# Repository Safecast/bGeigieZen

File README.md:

# bGeigieZen

A modern radiation monitoring device based on the M5Stack hardware platform, developed by the Safecast community.

## Overview

bGeigieZen is a portable radiation monitoring device that combines precision sensing with a user-friendly interface. Built on the M5Stack platform, it provides real-time radiation measurements with GPS logging capabilities.

## Features

- Real-time radiation monitoring
- GPS location tracking
- Data logging to SD card
- User-friendly display interface
- Long battery life
- Mobile app connectivity
- Compatible with the Safecast API

## Hardware Requirements

- M5Stack Core device (Core2 or CoreS3)
- LND-7317 radiation sensor
- GPS module (see [Supported GPS Modules](#supported-gps-modules) below)
- SD card for logging

## Supported GPS Modules

The firmware supports u-blox GPS modules over UART (Port C on M5Stack).

| Module | Chip | Protocol | Mode | Notes |
|---|---|---|---|---|
| Beitian BN-280 / BN-880 | u-blox M8 | UBX (bidirectional) | Full UBX | Default recommended module |
| u-blox NEO-M9N | u-blox M9 | UBX (bidirectional) | Full UBX | |
| u-blox NEO-M10 | u-blox M10 | UBX (bidirectional) | Full UBX | |
| u-blox NEO-7M / UBX-G7020-KT | u-blox M7 | NMEA (RX-only) or UBX | NMEA fallback or Full UBX | RX-only works with only GPS TX → CoreS3 GPIO18 connected; connect GPS RX → GPIO17 for full UBX |

### Wiring (M5Stack CoreS3 Port C)

| CoreS3 Port C pin | GPIO | Direction | Connect to |
|---|---|---|---|
| RXD | GPIO18 | ESP32 receives | GPS TX |
| TXD | GPIO17 | ESP32 transmits | GPS RX (optional — required for full UBX mode) |

**NMEA fallback mode:** If only the GPS TX → GPIO18 wire is connected (GPS RX is not wired), the firmware automatically detects this and switches to NMEA-only parsing. Coordinates, time, date, and satellite count are still reported. The status bar shows `GPS?` while searching, then the satellite count and fix state once acquired. Full UBX mode (both wires) is recommended for faster cold-start and richer data.

## Software Setup

1. **Install Required Development environment**
   - VS Code with PlatformIO or PlatformIO standalone

2. **Install Required Libraries**:
   - m5stack/M5Unified
   - claypuppet/SensorReporter
   - beakes/TeenyUbloxConnect
   - alextaujenis/RBD_Timer

3. **Clone the Repository**:
   ```bash
   git clone https://github.com/Safecast/bGeigieZen.git
   ```

## Building and Flashing

1. Open the project in VS Code with PlatformIO, or invoke PlatformIO from the shell/CMD.
2. Select your M5Stack board.
3. Compile and upload.

## Usage

1. Power on the device.
2. Wait for GPS signal acquisition.
3. Radiation measurements will display on screen.
4. Data logs automatically save to the SD card.

## Status Bar

The bottom status bar shows live device state at a glance:

| Indicator | Meaning |
|---|---|
| `GPS?` (orange) | GPS active, searching for satellites (cold start) |
| `GPS12` (orange) | GPS tracking 12 satellites, no fix yet |
| `GPS5` (green) | GPS fix acquired using 5 satellites |
| `GPS` (red) | GPS module not detected / error |
| `GM` (white) | Geiger tube active |
| `GM` (red) | Geiger tube required but not detected |
| `SD` (white/green) | SD card present and writeable |
| `SD` (red) | SD card required but missing or unreadable |
| `WF` (white/green) | Wi-Fi connected |
| `BT` (white/green) | Bluetooth active |
| `SN` (green) | Sound enabled |
| `#12345` | Device ID |

## SD card configuration files

This project references configuration files used by both bGeigie Nano and bGeigie Zen devices. They are different and not interchangeable. Use the appropriate file for your device:

### bGeigie Nano — `SAFECAST.TXT`

- Location: SD card root of a bGeigie Nano.
- Format: `key=value` per line. Example reference file: https://github.com/Safecast/bGeigieNanoKit/blob/master/SD%20card/SAFECAST.TXT

Common keys (with firmware semantics):
- `nm` — Profile name. Typically `SAFECAST`. Informational label, shown in menus/log headers.
- `did` — Device ID used by the Safecast ecosystem to associate logs/uploads. Required for proper identification. Range and format depend on Nano firmware and Safecast policy.
- `gt` — GPS type selector. `0` often means u‑blox; other values map to alternative GPS chipsets/modules. Used to configure serial baud, message set, and initialization.
- `gm` — GPS mode. Controls GPS operating/profile mode (e.g., cold/warm start preferences or power mode). Exact mapping is firmware‑specific.
- `cpmf` — CPM calibration factor (numeric). Multiplier applied to raw tube counts to compute calibrated CPM or uSv/h conversion path.
- `cpmn` — CPM factor name (text). Label for the calibration factor (e.g., `Cs137`) stored alongside logs.
- `bqmf` — Bq/m² calibration factor (numeric). Multiplier used when exporting in Bq/m² units.
- `bqmn` — Bq/m² factor name (text). Label for the Bq/m² factor (e.g., `Cs137`).
- `al` — Alert threshold in CPM. When current CPM ≥ `al`, the Nano emits an alert (beep/visual), depending on sound settings.
- `tz` — Timezone offset in hours from UTC. Example: `9` for JST. Used for local time stamping on device.
- `cn` — Country code (ISO‑3166). Often `JPN`, etc. May be embedded in file headers or used for region‑specific defaults.
- `st` — Logging start mode. `0` typically manual; non‑zero values may enable auto‑start or different trigger logic. Firmware‑dependent.
- `ss` — Sound setting. `0` off, `1` on (beeps/clicks). May offer additional levels on some firmware.
- `sh` — Screen brightness (0–100). Backlight level.
- `sm` — Screen/map mode. Selects UI layout or mapping behavior. Firmware‑dependent.
- `cw` — Commit/write interval in seconds. Controls how frequently log lines are flushed to SD.

Notes:
- Values and enumerations above reflect common Nano firmwares; refer to the Nano documentation for the definitive mapping.
- Consult the Nano repository for full semantics and latest defaults.

Sample templates:

- Minimal `SAFECAST.TXT` (Nano):

```ini
nm=SAFECAST
did=5555
al=100
tz=9
ss=1
cw=60
```

- Full `SAFECAST.TXT` example (Nano):

```ini
nm=SAFECAST
did=5555
gt=0
gm=0
cpmf=334
cpmn=Cs137
bqmf=37
bqmn=Cs137
al=100
tz=9
cn=JPN
st=0
ss=1
sh=100
sm=0
cw=60
```

References:
- Canonical example file in Nano kit: https://github.com/Safecast/bGeigieNanoKit/blob/master/SD%20card/SAFECAST.TXT
- Nano project docs and firmware should be consulted for exact enumerations and behavior.

### bGeigie Zen — `SAFEZEN.txt`

Every Zen device uses an SD card with a `SAFEZEN.txt` configuration file placed at the SD root. At minimum, you must set a valid `device_id` for the device to operate.

Quick start:
- See sample files in `SDcard/`:
  - `SDcard/minimal/SAFEZEN.txt` (minimal config with just `device_id`)
  - `SDcard/all_settings/SAFEZEN.txt` (example of all commonly supported fields)
- You can also manage all settings from the device: Menu → Settings (the device can read and write `SAFEZEN.txt`).

Supported settings (key=value per line):
- `version`
  - Optional firmware version marker written by the device. If missing, the current firmware attempts to parse using the latest format.
- `device_id`
  - Required. Must be between 5000 and 5999. The device will not operate without a valid ID in this range.
- `user_name`
  - Optional display and identification name used on-screen and in some outputs.
- `api_key`
  - Optional Safecast API key for uploading where applicable. The same key is used for api.safecast.org and simplemap.safecast.org.
- `simplemap_email`
  - Optional. Email address of your simplemap.safecast.org account. Together with `api_key` it is used to log in to simplemap and upload Real-time trip logs there (see `userdocs/rt-trip-logging.md`). If empty, trips are still uploaded to api.safecast.org but the simplemap step is retried and fails. Must come after `device_id` in the file, no spaces.
- `access_point_password`
  - Password for the device’s built-in Wi‑Fi Access Point (used by the configuration portal).
- `wifi_ssid`
  - Primary Wi‑Fi SSID for connecting to a local network.
- `wifi_password`
  - Password for `wifi_ssid`.
- `wifi_ssid2`
  - Secondary Wi‑Fi SSID profile (optional).
- `wifi_password2`
  - Password for `wifi_ssid2`.
- `wifi_profile`
  - Select active Wi‑Fi profile. `1` = use `wifi_ssid`/`wifi_password`. `2` = use `wifi_ssid2`/`wifi_password2`.
- `alert_threshold`
  - CPM alert threshold. Range 10–9999. Triggers audible and visual “CPM ALERT” when exceeded.
  - Note: Older examples may show `alarm_threshold`, but the current firmware uses `alert_threshold`.
  - See: [Zen Specification — Alerts](https://github.com/Safecast/bGeigieZen/wiki/Specification)
- `display_cpm`
  - Display unit selector. `1` = show CPM. `0` = show µSv/h.
- `manual_logging`
  - Logging behavior. `1` = manual start/stop. `0` = automatic depending on mode/movement.
  - See: [Zen Specification — Logging](https://github.com/Safecast/bGeigieZen/wiki/Specification)
- `enable_journal`
  - Enable the journal log. `1` = enabled, `0` = disabled.
  - See: [Zen Specification — Files & Journaling](https://github.com/Safecast/bGeigieZen/wiki/Specification)
- `log_void`
  - Include invalid/void lines in logs. `1` = include, `0` = exclude.
- `screen_dim_timeout`
  - Seconds of inactivity before screen dims.
  - See: [Zen Specification — Display & Power](https://github.com/Safecast/bGeigieZen/wiki/Specification)
- `screen_off_timeout`
  - Seconds of inactivity before screen turns off.
  - See: [Zen Specification — Display & Power](https://github.com/Safecast/bGeigieZen/wiki/Specification)
- `animated_screensaver`
  - Screensaver animation on dim/off. `1` = enabled, `0` = disabled.
  - See: [Zen Specification — Display & Power](https://github.com/Safecast/bGeigieZen/wiki/Specification)
- `error_alert_sound`
  - Error beep sounds. `1` = enabled, `0` = disabled.
  - See: [Zen Specification — Alerts](https://github.com/Safecast/bGeigieZen/wiki/Specification)
- `dim_brightness`
  - Brightness level (0–100) used while dimmed/screensaver.
- `audio_volume`
  - Global audio volume (0–100) for clicks and alerts.
- `fixed_latitude`
  - Latitude used in Fixed mode.
- `fixed_longitude`
  - Longitude used in Fixed mode.
- `fixed_range`
  - Radius in km for Fixed mode validity.
- `dop_max`
  - Maximum acceptable Dilution of Precision (DOP) for GPS fix validity.
  - See: [Zen Specification — GPS & Accuracy](https://github.com/Safecast/bGeigieZen/wiki/Specification)

Notes:
- Unknown or unsupported lines are ignored by the firmware.
- Settings changed from the device UI are persisted to internal memory and can be written back to `SAFEZEN.txt` via Settings → “Save to SD”.
- The device also supports configuring via Wi‑Fi using the built-in Access Point or a local network (see Settings screen).

### Nano ↔ Zen quick comparison (overlapping concepts)

| Concept | bGeigie Nano (SAFECAST.TXT) | bGeigie Zen (SAFEZEN.txt) |
| --- | --- | --- |
| Device ID | `did` (format/range Nano‑specific) | `device_id` (required, 5000–5999) |
| Alert threshold (CPM) | `al` | `alert_threshold` |
| Timezone | `tz` (hours offset) | not required; Zen uses RTC and can show local time; timezone not needed for logging |
| Display units | n/a (Nano UI dependent) | `display_cpm` (1=CPM, 0=µSv/h) |
| Wi‑Fi/API | n/a in Nano SAFECAST | `wifi_*`, `api_key`, `access_point_password` |
| Logging behavior | `st`/`cw` (start mode and commit interval) | `manual_logging` (manual vs auto), commit policy handled by firmware |
| GPS accuracy threshold | n/a (implicit) | `dop_max` (DOP limit) |
| Fixed location | n/a | `fixed_latitude`, `fixed_longitude`, `fixed_range` |
| Brightness & power | `sh` (0–100) | `dim_brightness`, `screen_dim_timeout`, `screen_off_timeout`, `animated_screensaver` |
| Sound & alerts | `ss` (0/1) | `error_alert_sound`, `audio_volume`, `alert_threshold` |

Tip: These files are not interchangeable. Use `SAFECAST.TXT` on Nano, and `SAFEZEN.txt` on Zen.

## Contributing

We welcome contributions! Please follow these steps:

1. Fork the repository.
2. Create a feature branch.
3. Submit a Pull Request.

## License

This project is licensed under the MIT License.

## Support

- Visit [Safecast.org](https://safecast.org)
- Join our community forums
- Report issues on GitHub

## Credits

Developed and maintained by the Safecast community.

- Specifications: [bGeigieZen Wiki](https://github.com/Safecast/bGeigieZen/wiki/Specification)
- Full documentation: [bgeigiezen.safecast.jp](https://bgeigiezen.safecast.jp)

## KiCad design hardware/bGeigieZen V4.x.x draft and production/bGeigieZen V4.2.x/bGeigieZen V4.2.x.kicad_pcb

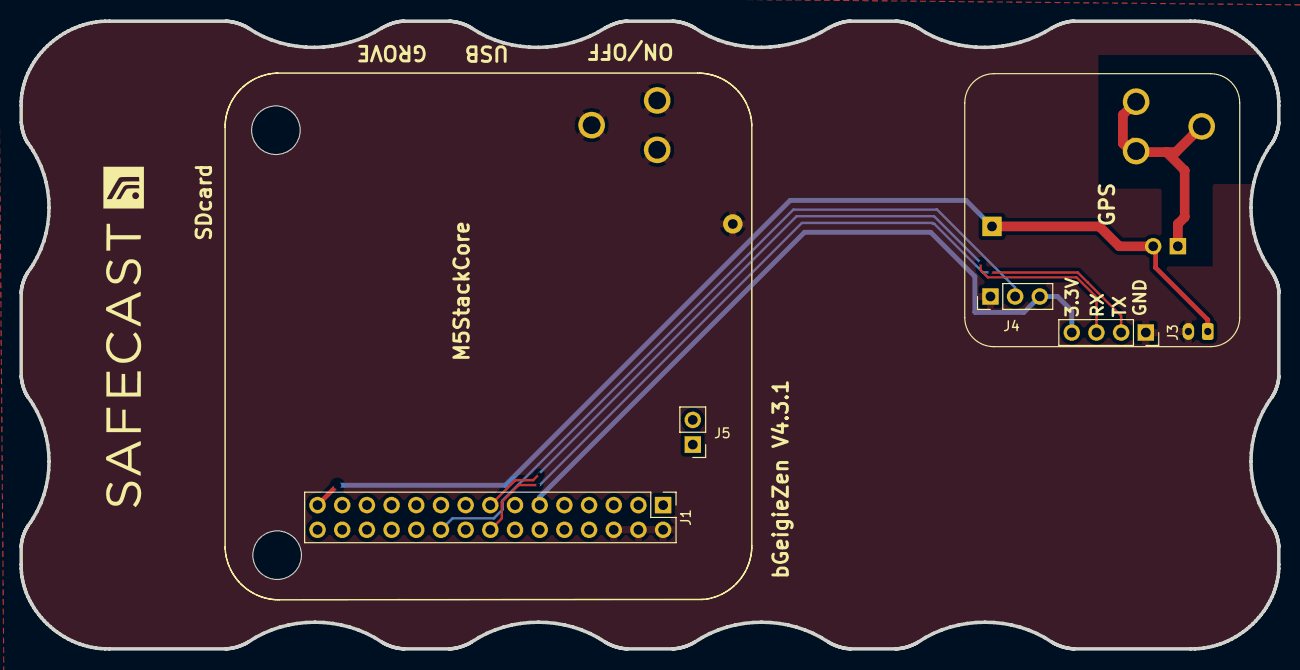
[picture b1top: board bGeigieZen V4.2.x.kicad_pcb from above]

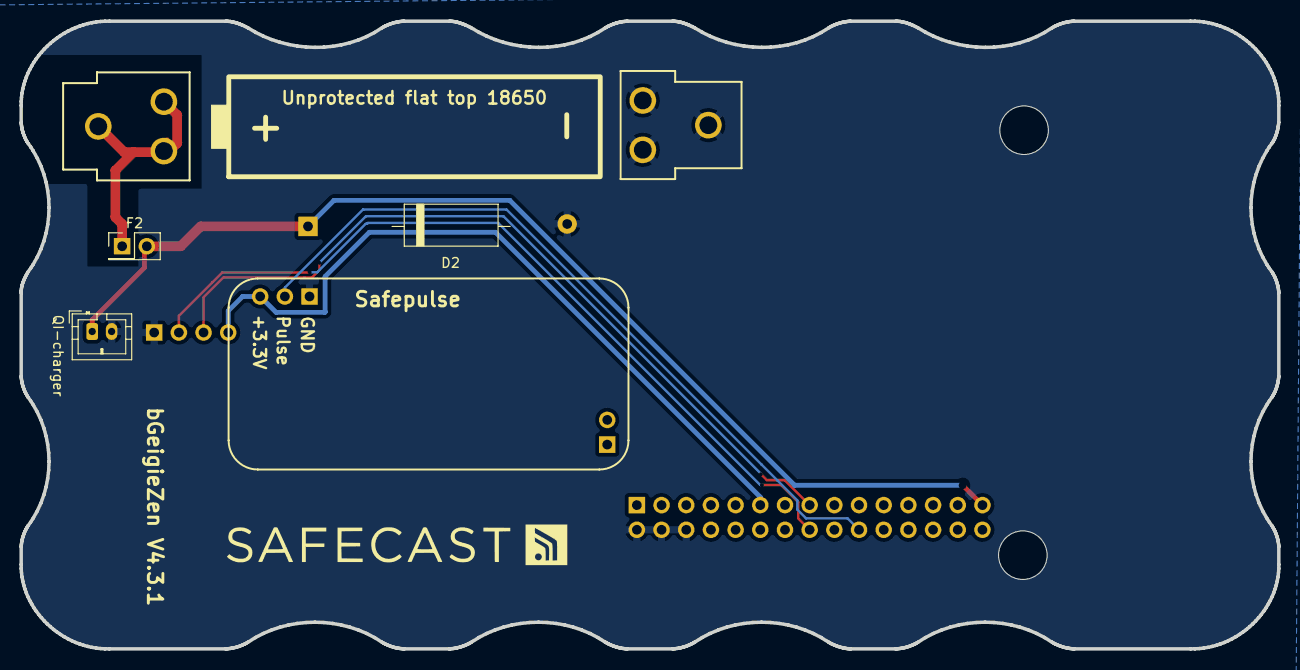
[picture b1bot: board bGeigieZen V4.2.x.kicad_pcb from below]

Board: 2 copper layers, 129.4 x 64.6 mm, 12 parts (5 on the bottom side), 7 nets.

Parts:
BT1: 3.7 V Lipo; BATTERY_18650-HOLDER
D2: Crowbar; D_DO-201_P15.24mm_Horizontal
F2: Polyfuse; PinHeader_2x01_P2.54mm_Vertical
G back: LOGO
G front: LOGO
H4, H6: MountingHole_Pad; MountingHole_3.2mm_M3
J1: M5 2x15 pin; PinHeader_2x15_P2.54mm_Vertical
J3: GPS; PinSocket_1x04_P2.54mm_Vertical
J4: Geiger Safepulse; PinHeader_1x03_P2.54mm_Vertical
J5: Extra support header; PinHeader_1x02_P2.54mm_Vertical
QI-charger: QI GND; JST_PH_B2B-PH-K_1x02_P2.00mm_Vertical

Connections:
3.3V: J1.11, J3.4, J4.3
/BAT: D2.1 (K), F2.2, J1.29, QI-charger.1
/GIO2 on Core and GIO32 on Core-2: J1.20, J4.2
/RX2: J1.15, J3.3
/TX2: J1.16, J3.2
GND: BT1.1 (+), BT1.PWR@2, BT1.PWR@3, D2.2 (A), J1.2, J1.4, J1.6, J3.1, J4.1, QI-charger.2
unnamed: BT1.1 (+), F2.1

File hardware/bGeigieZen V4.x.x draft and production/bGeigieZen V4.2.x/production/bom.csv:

Designator,Footprint,Quantity,Value,LCSC Part #
BT1,BATTERY_18650-HOLDER,1,3.7 V Lipo,
D2,D_DO-201_P15.24mm_Horizontal,1,Crowbar,
F2,PinHeader_2x01_P2.54mm_Vertical,1,Polyfuse,
"H4, H6",MountingHole_3.2mm_M3,2,MountingHole_Pad,
J1,PinHeader_2x15_P2.54mm_Vertical,1,M5 2x15 pin,
J3,PinSocket_1x04_P2.54mm_Vertical,1,GPS,
J4,PinHeader_1x03_P2.54mm_Vertical,1,Geiger Safepulse,
J5,PinHeader_1x02_P2.54mm_Vertical,1,Extra support header,
QI-CHARGER,JST_PH_B2B-PH-K_1x02_P2.00mm_Vertical,1,QI GND,

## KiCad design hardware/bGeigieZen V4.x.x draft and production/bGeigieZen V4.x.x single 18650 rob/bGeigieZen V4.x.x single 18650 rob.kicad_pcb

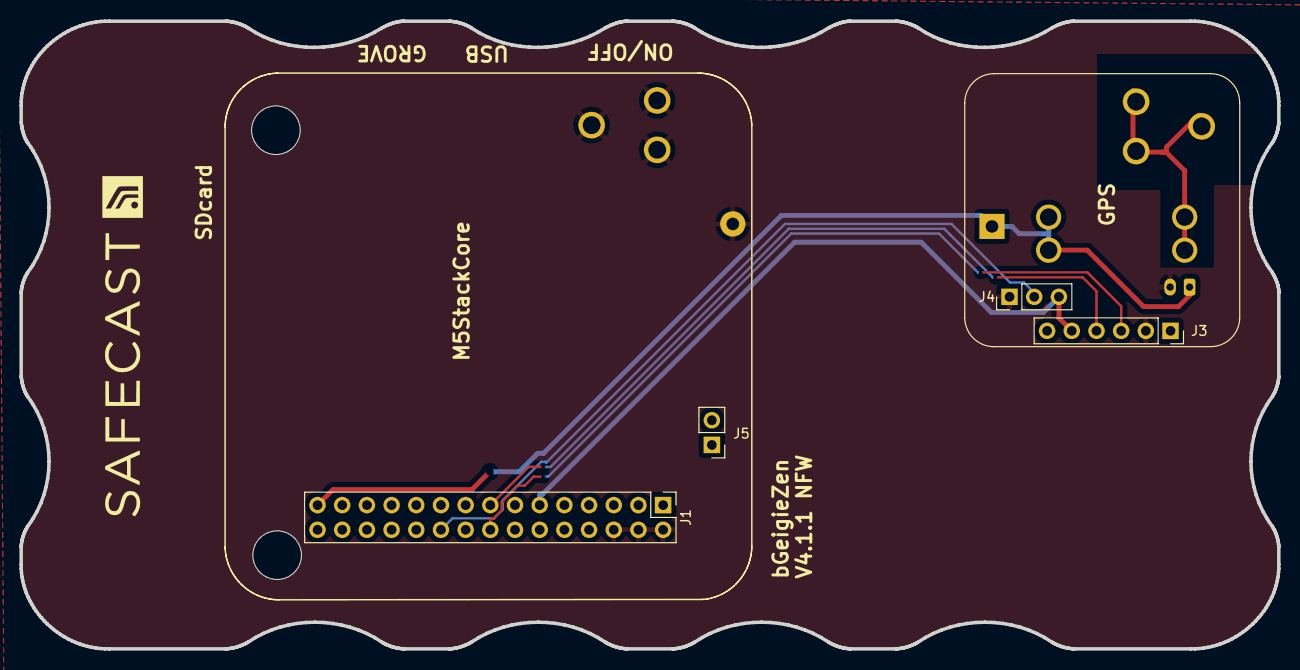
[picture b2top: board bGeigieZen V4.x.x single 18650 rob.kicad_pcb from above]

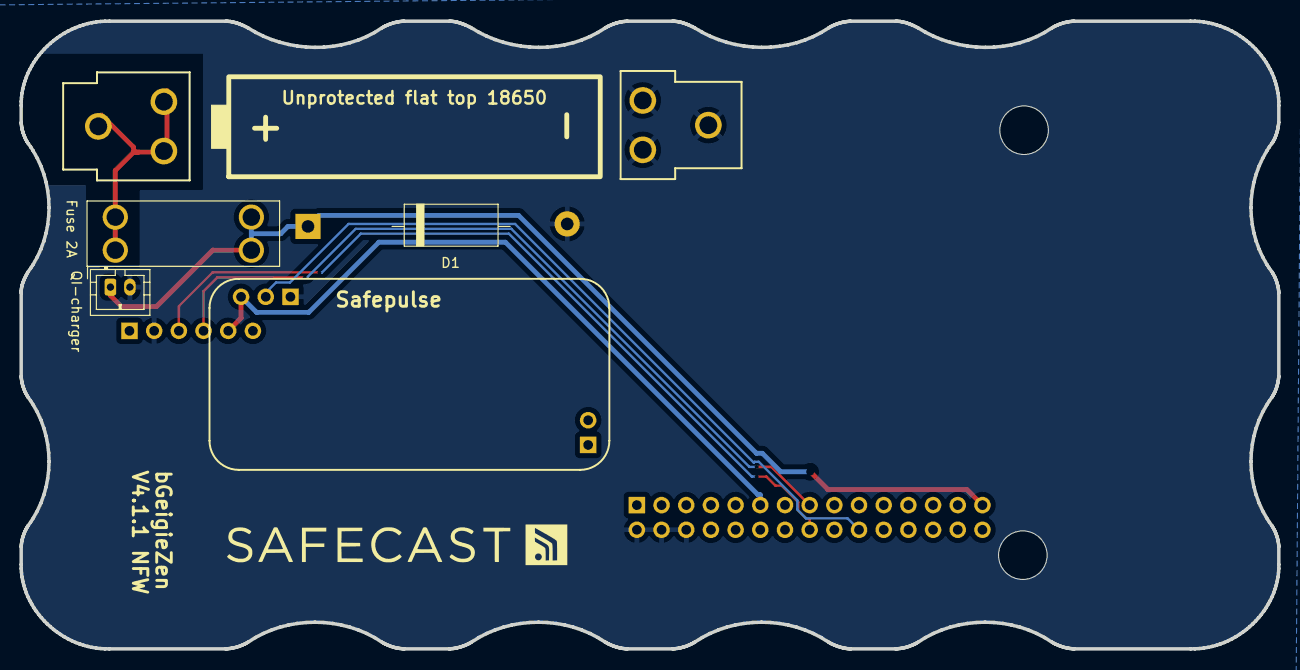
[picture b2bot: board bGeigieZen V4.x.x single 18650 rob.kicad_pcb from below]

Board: 2 copper layers, 129.4 x 64.6 mm, 12 parts (5 on the bottom side), 7 nets.

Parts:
BT1: 3.7 V Lipo; BATTERY_18650-HOLDER
D1: Crowbar; D_DO-201_P15.24mm_Horizontal
Fuse 2A: Fuse_Small; FUSE_3557-2
G back: LOGO
G front: LOGO
H4, H6: MountingHole_Pad; MountingHole_3.2mm_M3
J1: M5 2x15 pin; PinHeader_2x15_P2.54mm_Vertical
J3: GPS; PinSocket_1x06_P2.54mm_Vertical
J4: Geiger Safepulse; PinHeader_1x03_P2.54mm_Vertical
J5: Extra support header; PinHeader_1x02_P2.54mm_Vertical
QI-charger: QI GND; JST_PH_B2B-PH-K_1x02_P2.00mm_Vertical

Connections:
3.3V: J1.11, J3.5, J4.3
/BAT: D1.1 (K), Fuse 2A.2, J1.29, QI-charger.1
/GIO2 on Core and GIO32 on Core-2: J1.20, J4.2
/RX2: J1.15, J3.4
/TX2: J1.16, J3.3
GND: BT1.1 (+), BT1.PWR@2, BT1.PWR@3, D1.2 (A), J1.2, J1.4, J1.6, J3.2, J4.1, QI-charger.2
unnamed: BT1.1 (+), BT1.PWR@2, BT1.PWR@3, Fuse 2A.1

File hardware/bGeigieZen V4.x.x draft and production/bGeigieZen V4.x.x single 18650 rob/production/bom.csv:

Designator,Footprint,Quantity,Value,LCSC Part #
BT1,BATTERY_18650-HOLDER,1,3.7 V Lipo,
D1,D_DO-201_P15.24mm_Horizontal,1,Crowbar,
FUSE 2A,FUSE_3557-2,1,Fuse_Small,
"H4, H6",MountingHole_3.2mm_M3,2,MountingHole_Pad,
J1,PinHeader_2x15_P2.54mm_Vertical,1,M5 2x15 pin,
J3,PinSocket_1x06_P2.54mm_Vertical,1,GPS,
J4,PinHeader_1x03_P2.54mm_Vertical,1,Geiger Safepulse,
J5,PinHeader_1x02_P2.54mm_Vertical,1,Extra support header,
QI-CHARGER,JST_PH_B2B-PH-K_1x02_P2.00mm_Vertical,1,QI GND,

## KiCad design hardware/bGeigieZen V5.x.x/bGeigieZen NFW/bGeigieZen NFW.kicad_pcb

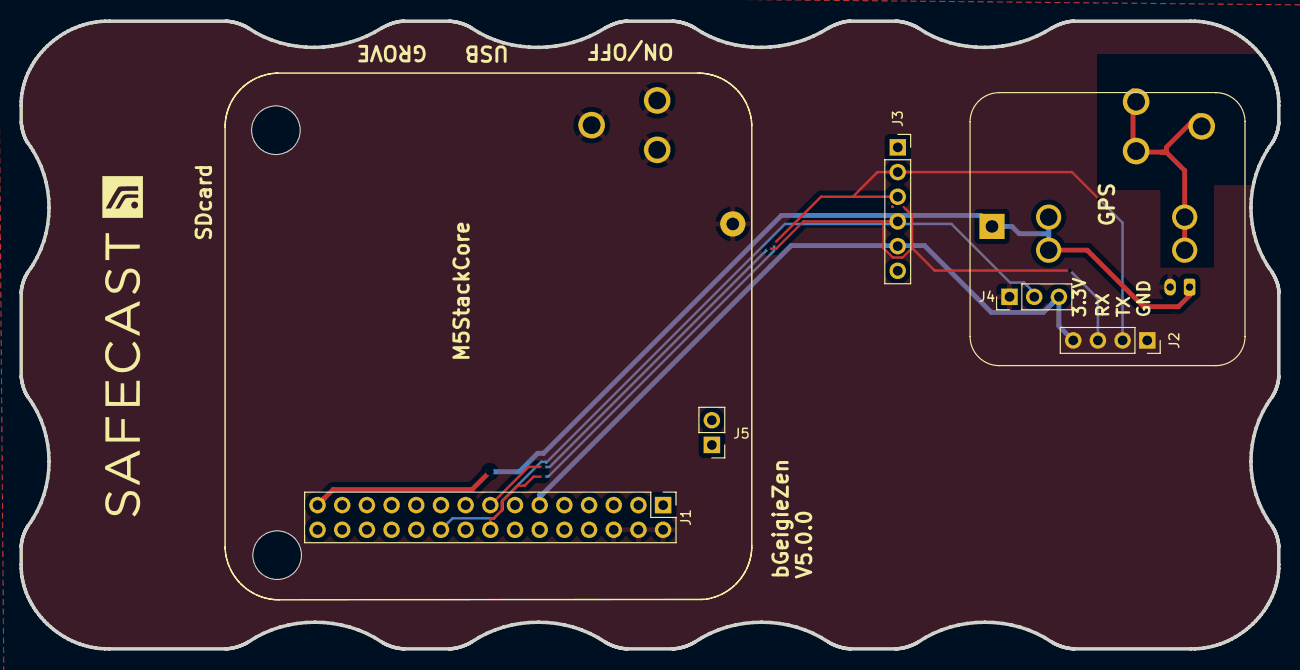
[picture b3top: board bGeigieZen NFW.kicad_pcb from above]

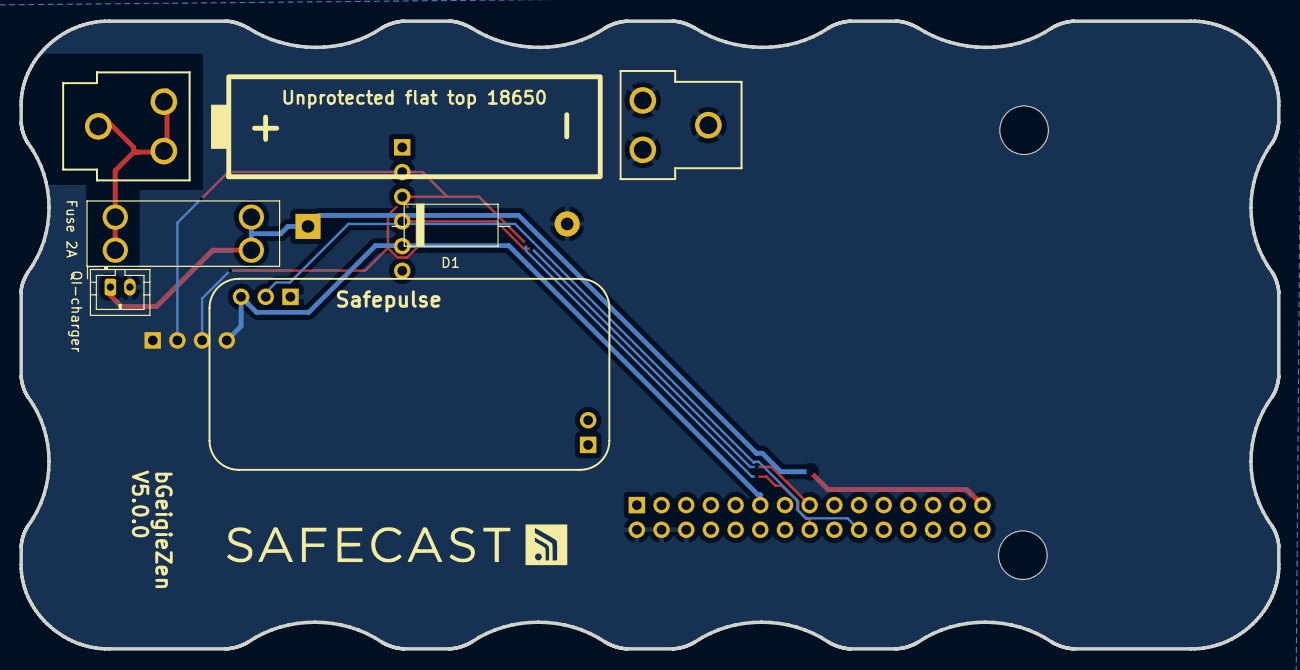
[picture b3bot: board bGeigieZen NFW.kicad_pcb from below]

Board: 2 copper layers, 129.4 x 64.6 mm, 13 parts (5 on the bottom side), 7 nets.

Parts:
BT1: 3.7 V Lipo; BATTERY_18650-HOLDER
D1: Crowbar; D_DO-201_P15.24mm_Horizontal
Fuse 2A: Fuse_Small; FUSE_3557-2
G back: LOGO
G front: LOGO
H4, H6: MountingHole_Pad; MountingHole_3.2mm_M3
J1: M5 2x15 pin; PinHeader_2x15_P2.54mm_Vertical
J2: GPS; PinSocket_1x04_P2.54mm_Vertical
J3: Notecard; PinSocket_1x06_P2.54mm_Vertical
J4: Geiger Safepulse; PinHeader_1x03_P2.54mm_Vertical
J5: Extra support header; PinHeader_1x02_P2.54mm_Vertical
QI-charger: QI GND; JST_PH_B2B-PH-K_1x02_P2.00mm_Vertical

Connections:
3.3V: J1.11, J2.4, J3.4, J4.3
/BAT: D1.1 (K), Fuse 2A.2, J1.29, QI-charger.1
/GIO2 on Core and GIO32 on Core-2: J1.20, J4.2
/RX2: J1.15, J2.3, J3.3
/TX2: J1.16, J2.2, J3.2
GND: D1.2 (A), J1.2, J1.4, J1.6, J2.1, J3.1, J4.1, QI-charger.2
unnamed: BT1.1 (+), Fuse 2A.1

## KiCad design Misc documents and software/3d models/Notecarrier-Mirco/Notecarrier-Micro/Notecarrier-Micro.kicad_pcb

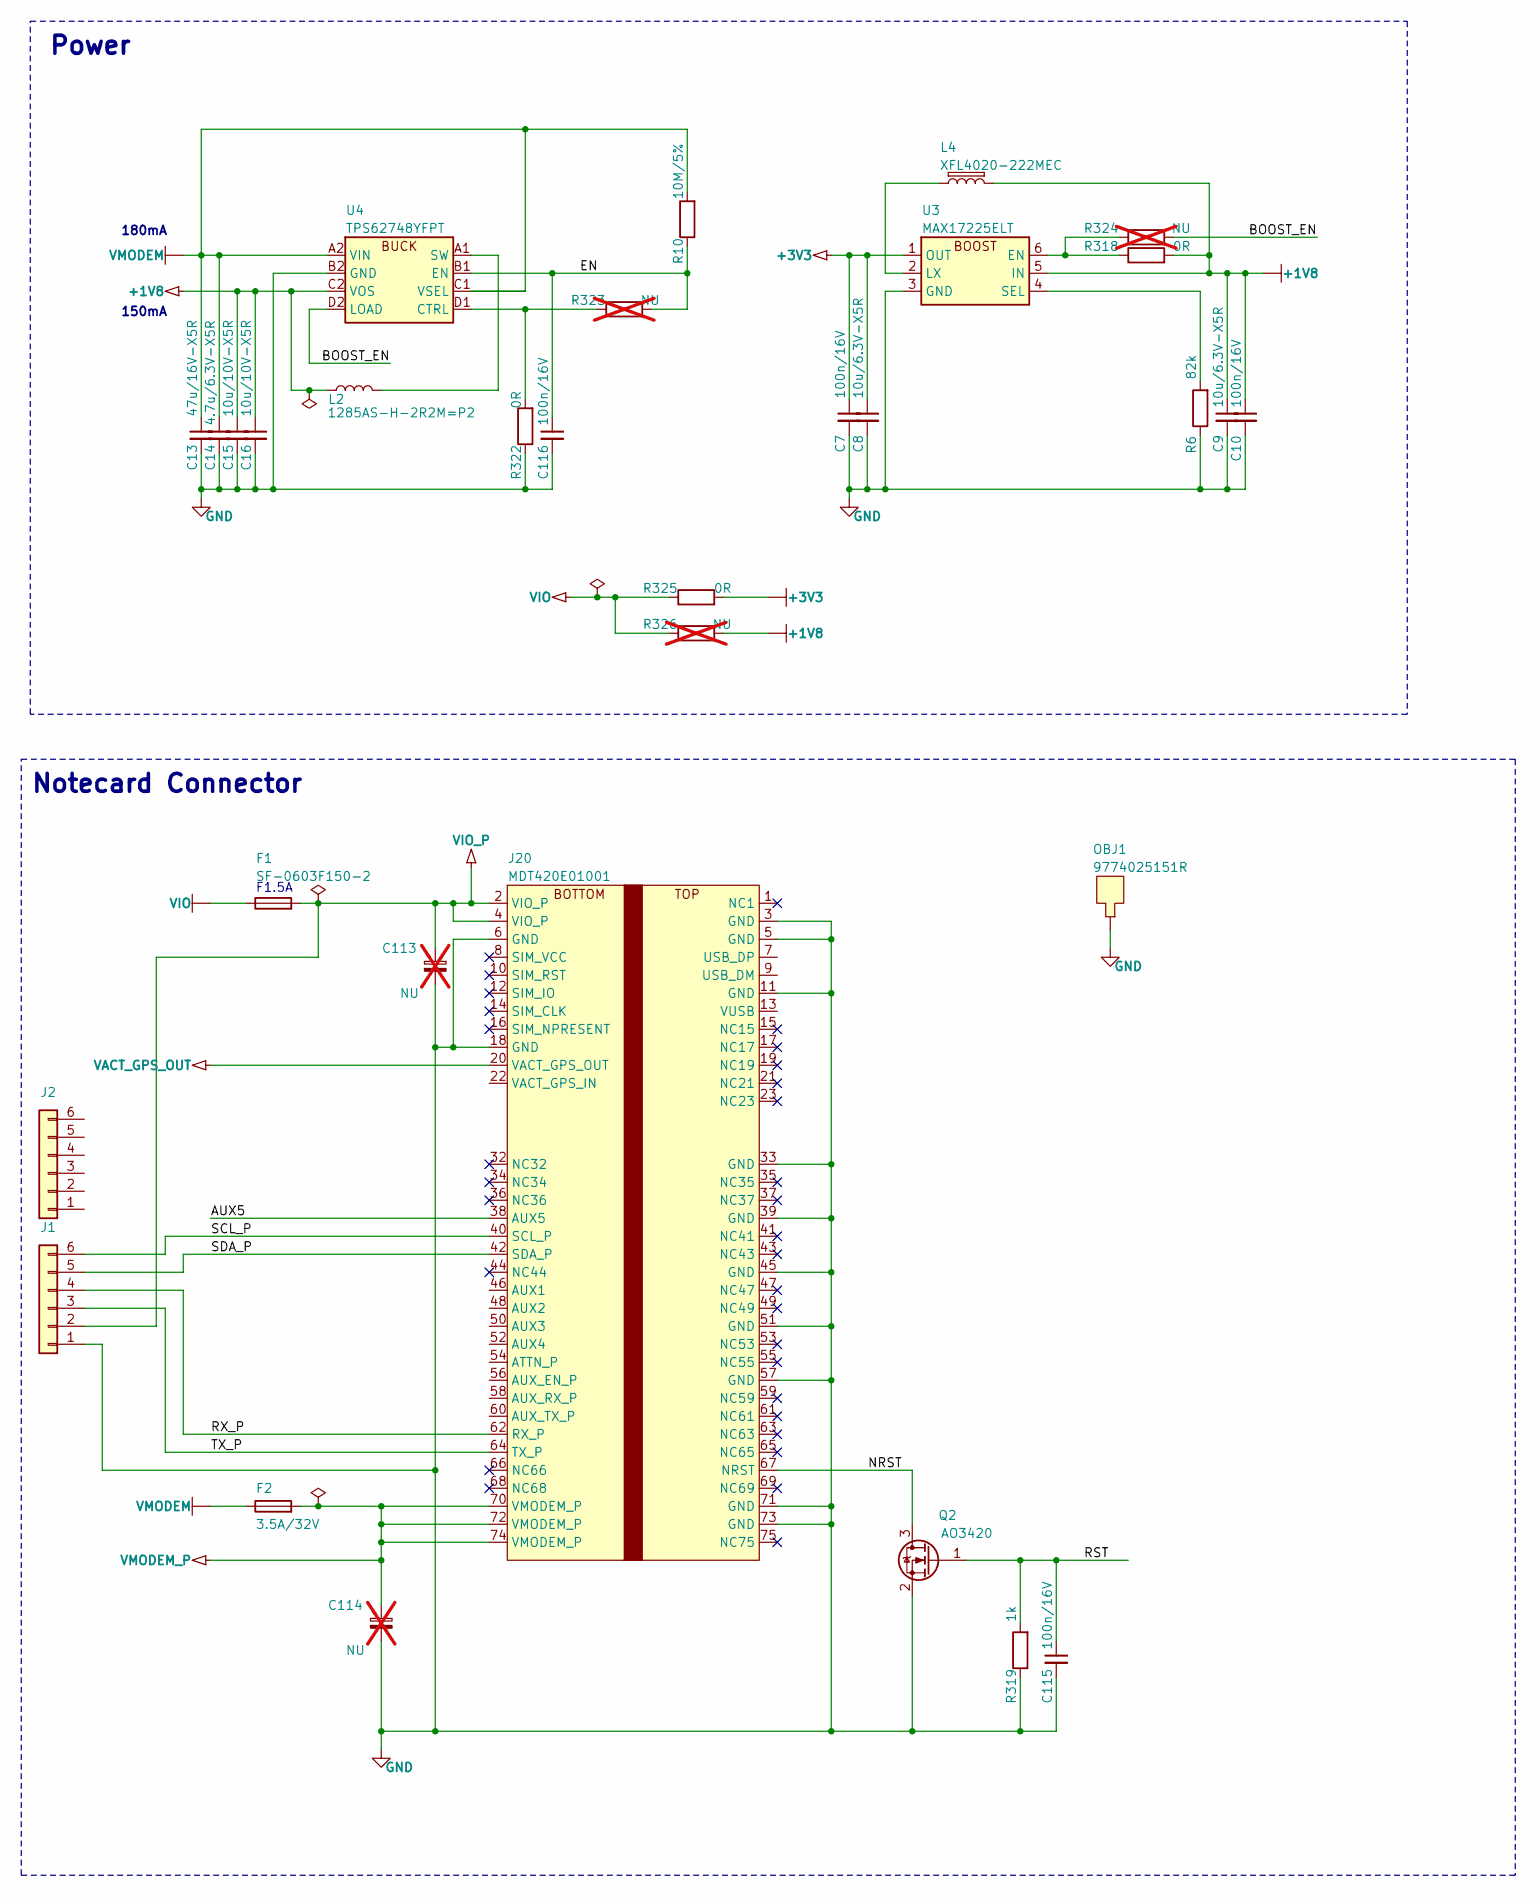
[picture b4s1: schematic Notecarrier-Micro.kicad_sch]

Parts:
C7, C10, C115, C116: 100n/16V; CS-C-0402_NO-FILL
C8, C9: 10u/6.3V-X5R; CS-C-0402_NO-FILL
C13: 47u/16V-X5R; CS-C-1206
C14: 4.7u/6.3V-X5R; CS-C-0402_NO-FILL
C15, C16: 10u/10V-X5R; CS-C-0603
C113: NU; CS-T-A; MPN F930J107KAA; not fitted
C114: NU; CS-T-B; MPN F930J227KBA; not fitted
F1: SF-0603F150-2; FS-0603; MPN SF-0603F150-2
F2: 3.5A/32V; FS-0603; MPN 0603SFV350F/32-2
J1, J2: Conn_01x06; PinHeader_1x06_P2.54mm_Vertical
J20: MDT420E01001; J-75-0050-MOS-M2-E
L2: 1285AS-H-2R2M=P2; LS-0806; MPN 1285AS-H-2R2M=P2
L4: XFL4020-222MEC; LS-XFL4020; MPN XFL4020-222MEC
OBJ1: 9774025151R; DIST-WASMSIM0250
Q2: AO3420; SOT23_NO-FILL
R6: 82k; RS-0402_NO-FILL
R10: 10M/5%; RS-0402_NO-FILL
R318, R322, R325: 0R; RS-0402_NO-FILL
R319: 1k; RS-0402_NO-FILL
R323, R324, R326: NU; RS-0402_NO-FILL; not fitted
U3: MAX17225ELT; WDFN6-0200X0200; MPN MAX17225ELT+T
U4: TPS62748YFPT; XFBGA8; MPN TPS62748YFPT

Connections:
+1V8: C9.1, C10.1, C15.1, C16.1, L2.2, L4.2, R318.2, R326.2, U3.5 (IN), U4.C2 (VOS)
+3V3: C7.1, C8.1, R325.2, U3.1 (OUT)
/AUX5: J20.38 (AUX5)
/BOOST_EN: R324.2, U4.D2 (LOAD)
/EN: C116.1, R10.1, R323.2, U4.B1 (EN)
/NRST: J20.67 (NRST), Q2.3 (D)
/RST: C115.1, Q2.1 (G), R319.2
/RX_P: J1.4, J20.62 (RX_P)
/SCL_P: J1.6, J20.40 (SCL_P)
/SDA_P: J1.5, J20.42 (SDA_P)
/TX_P: J1.3, J20.64 (TX_P)
GND: C7.2, C8.2, C9.2, C10.2, C13.2, C14.2, C15.2, C16.2, C113.2, C114.2, C115.2, C116.2, J1.1, J20.3 (GND), J20.5 (GND), J20.6 (GND), J20.11 (GND), J20.18 (GND), J20.33 (GND), J20.39 (GND), J20.45 (GND), J20.51 (GND), J20.57 (GND), J20.71 (GND), J20.73 (GND), OBJ1.1, Q2.2 (S), R6.1, R319.1, R322.1, U3.3 (GND), U4.B2 (GND)
unnamed: R318.1, R324.1, U3.6 (EN)
unnamed: L4.1, U3.2 (LX)
unnamed: R6.2, U3.4 (SEL)
unnamed: R322.2, R323.1, U4.D1 (CTRL)
unnamed: L2.1, U4.A1 (SW)
VACT_GPS_OUT: J20.20 (VACT_GPS_OUT)
VIO: F1.1, R325.1, R326.1
VIO_P: C113.1, F1.2, J1.2, J20.2 (VIO_P), J20.4 (VIO_P)
VMODEM: C13.1, C14.1, F2.1, R10.2, U4.A2 (VIN), U4.C1 (VSEL)
VMODEM_P: C114.1, F2.2, J20.70 (VMODEM_P), J20.72 (VMODEM_P), J20.74 (VMODEM_P)

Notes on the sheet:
150mA
180mA
F1.5A
Notecard Connector
Power

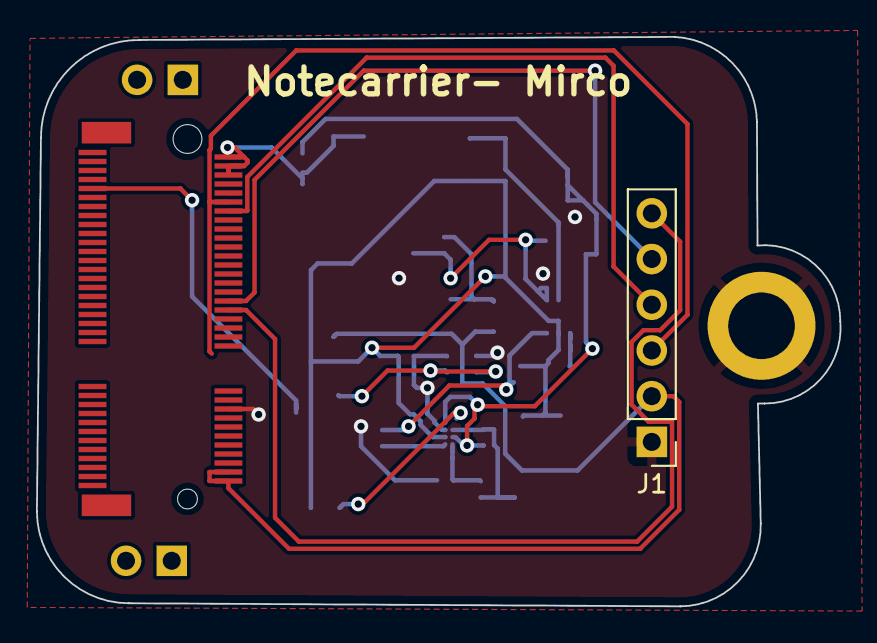
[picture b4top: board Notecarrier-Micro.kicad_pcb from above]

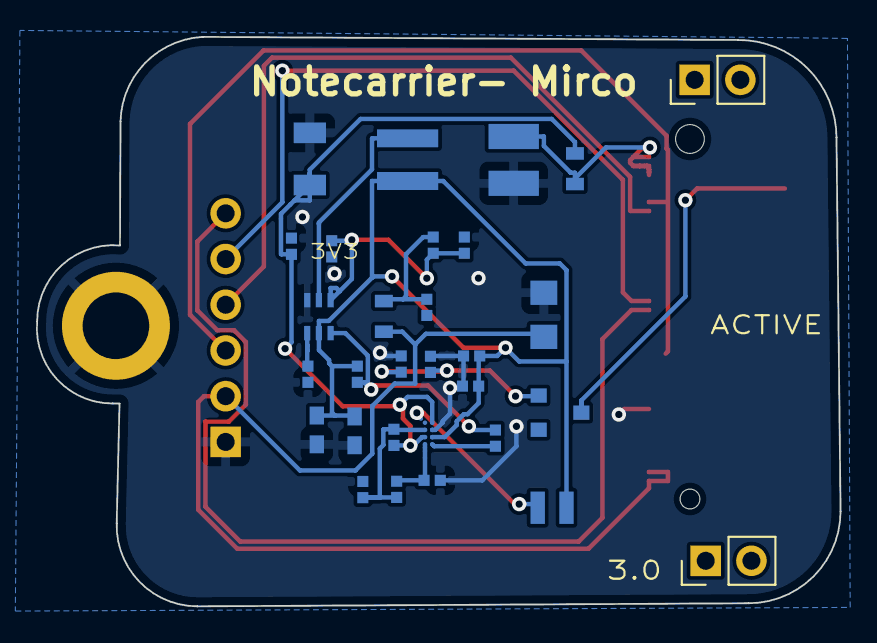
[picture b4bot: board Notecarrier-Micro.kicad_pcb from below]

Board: 11 copper layers, 44.6 x 31.6 mm, 33 parts (30 on the bottom side), 20 nets.

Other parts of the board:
Extra_pin_1, Extra_pin_2: PinHeader_1x02_P2.54mm_Vertical

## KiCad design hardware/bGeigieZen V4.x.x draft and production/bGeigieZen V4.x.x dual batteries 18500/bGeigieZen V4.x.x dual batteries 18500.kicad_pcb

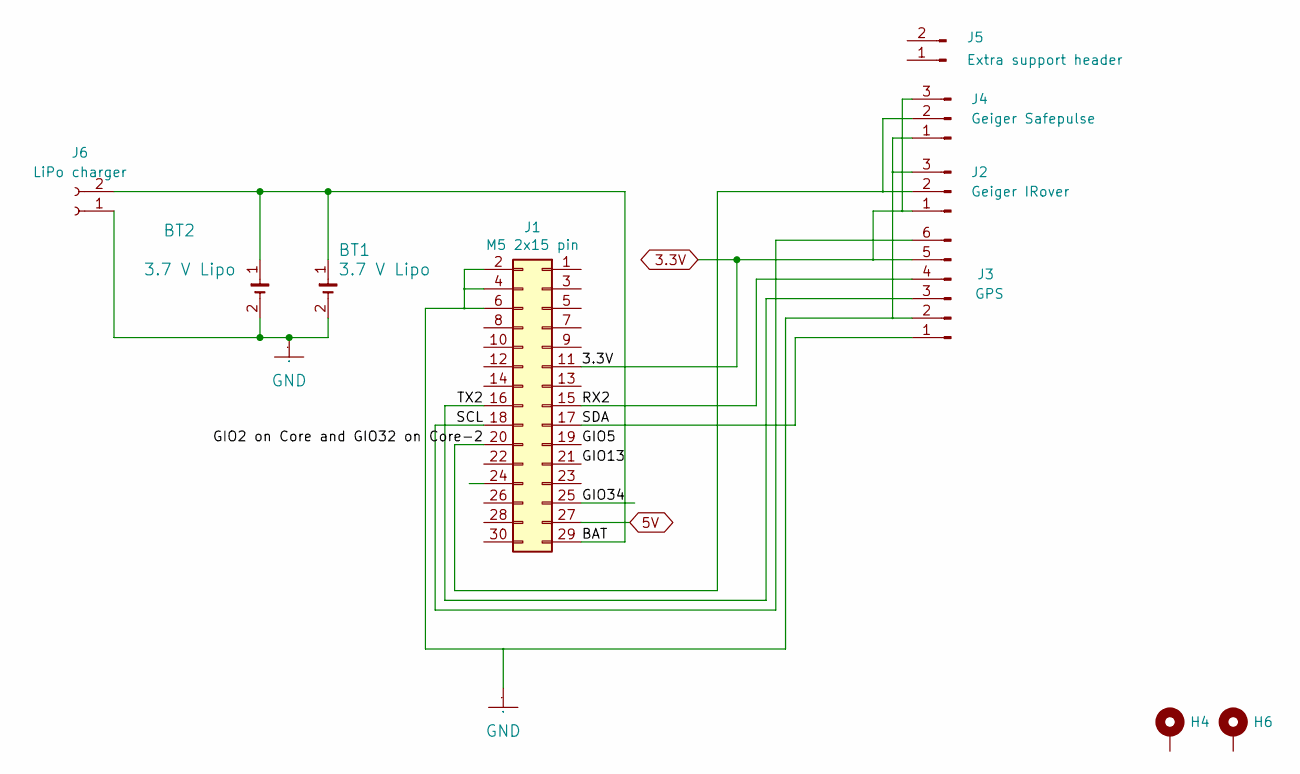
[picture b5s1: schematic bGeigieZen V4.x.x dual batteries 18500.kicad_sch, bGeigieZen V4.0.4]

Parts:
BT1, BT2: 3.7 V Lipo; BATTERY_18650-HOLDER
H4, H6: MountingHole_Pad; MountingHole_3.2mm_M3
J1: M5 2x15 pin; PinHeader_2x15_P2.54mm_Vertical
J2: Geiger IRover; PinHeader_1x03_P2.54mm_Vertical
J3: GPS; PinSocket_1x06_P2.54mm_Vertical
J4: Geiger Safepulse; PinHeader_1x03_P2.54mm_Vertical
J5: Extra support header; PinHeader_1x02_P2.54mm_Vertical
J6: LiPo charger; JST_PH_B2B-PH-K_1x02_P2.00mm_Vertical

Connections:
3.3V: J1.11, J2.1, J3.5, J4.3
5V: J1.27
/BAT: BT1.1 (+), BT2.1 (+), J1.29, J6.2
/GIO2 on Core and GIO32 on Core-2: J1.20, J2.2, J4.2
/GIO5: J1.19
/GIO13: J1.21
/GIO34: J1.25
/RX2: J1.15, J3.4
/SCL: J1.18, J3.6
/SDA: J1.17, J3.1
/TX2: J1.16, J3.3
GND: BT1.2 (-), BT2.2 (-), J1.2, J1.4, J1.6, J2.3, J3.2, J4.1, J6.1

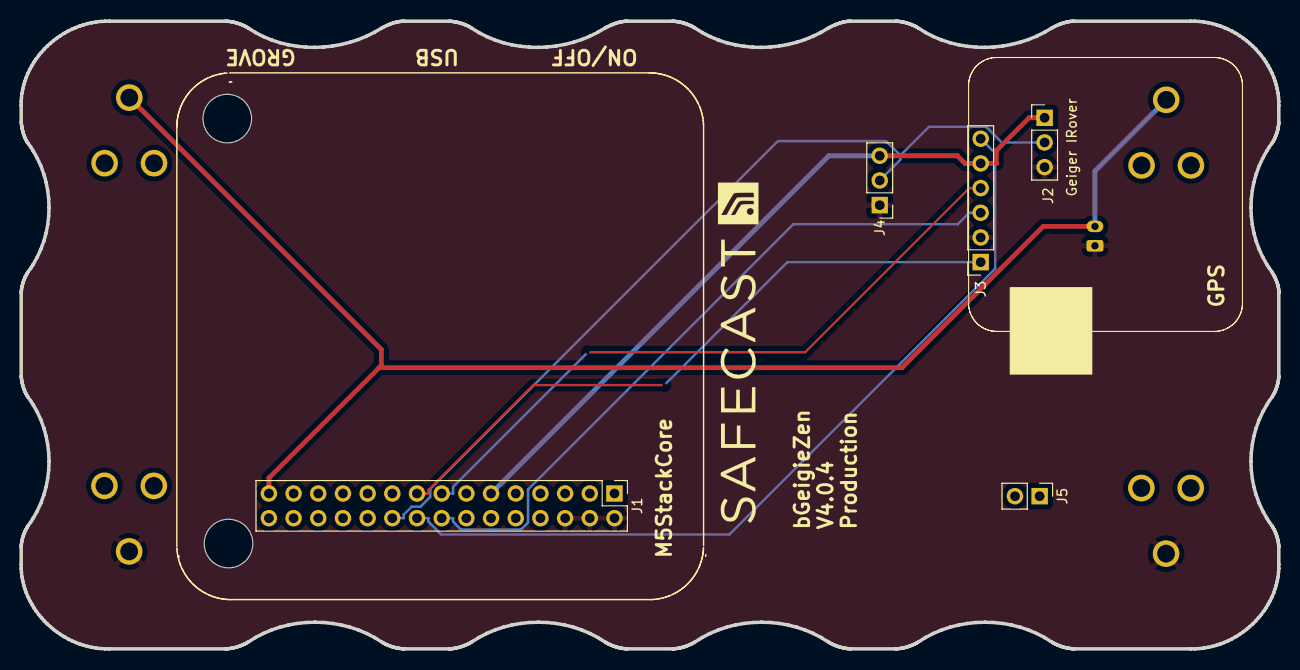
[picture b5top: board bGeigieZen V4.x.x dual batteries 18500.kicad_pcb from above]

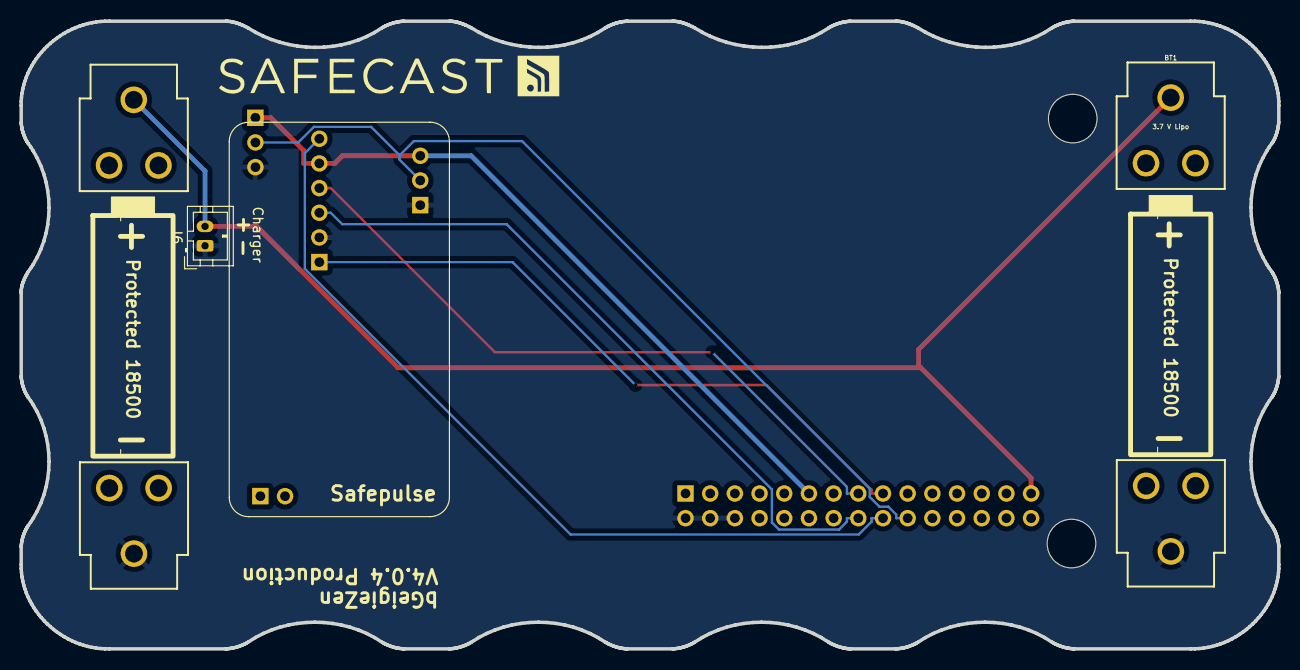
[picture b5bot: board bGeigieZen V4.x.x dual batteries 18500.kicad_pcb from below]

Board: 2 copper layers, 129.4 x 64.6 mm, 12 parts (4 on the bottom side), 8 nets.

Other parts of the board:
G back: LOGO
G front: LOGO

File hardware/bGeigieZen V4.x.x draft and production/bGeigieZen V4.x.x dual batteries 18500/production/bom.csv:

Designator,Footprint,Quantity,Value,LCSC Part #
"BT1, BT2",BATTERY_18650-HOLDER,2, 3.7 V Lipo,
"H4, H6",MountingHole_3.2mm_M3,2,MountingHole_Pad,
J1,PinHeader_2x15_P2.54mm_Vertical,1,M5 2x15 pin,
J2,PinHeader_1x03_P2.54mm_Vertical,1,Geiger IRover,
J3,PinSocket_1x06_P2.54mm_Vertical,1,GPS,
J4,PinHeader_1x03_P2.54mm_Vertical,1,Geiger Safepulse,
J5,PinHeader_1x02_P2.54mm_Vertical,1,Extra support header,

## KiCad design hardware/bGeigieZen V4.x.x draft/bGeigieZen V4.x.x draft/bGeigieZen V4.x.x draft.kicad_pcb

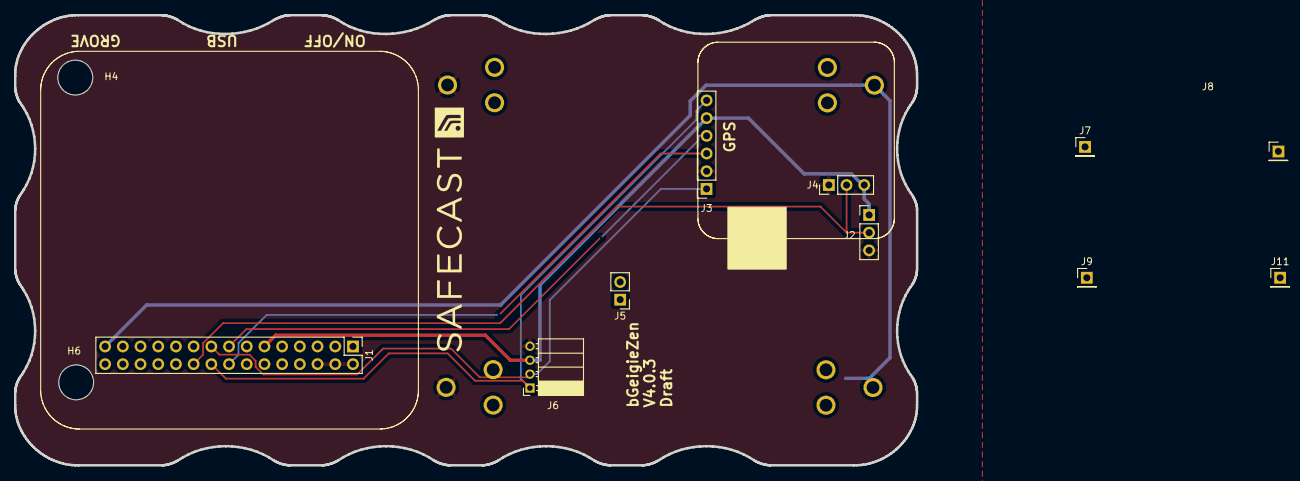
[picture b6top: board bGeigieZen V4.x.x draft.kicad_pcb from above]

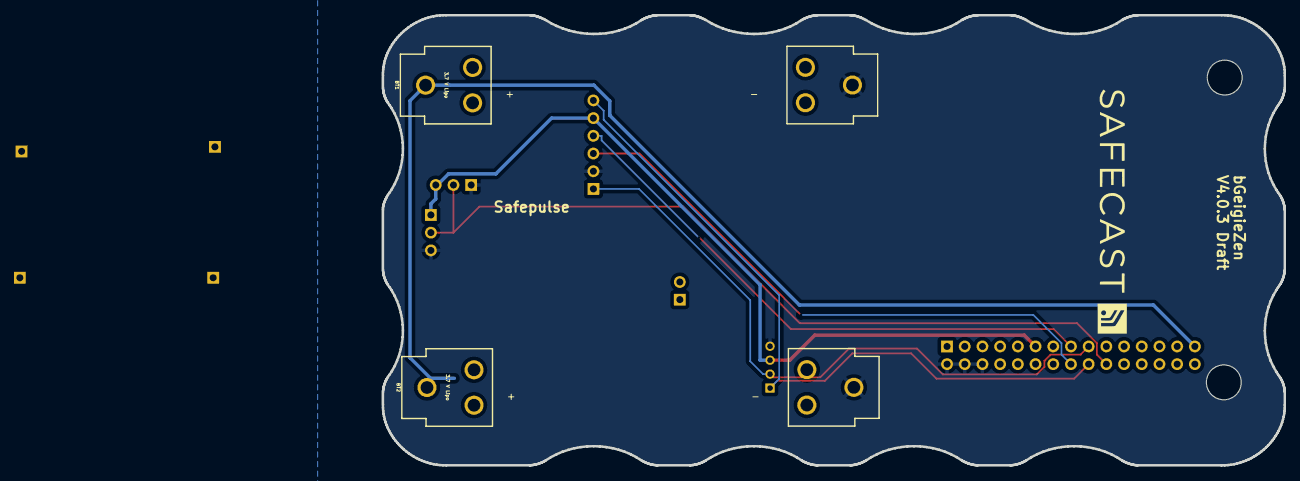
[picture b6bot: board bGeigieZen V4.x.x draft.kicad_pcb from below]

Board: 2 copper layers, 129.4 x 64.6 mm, 16 parts (3 on the bottom side), 8 nets.

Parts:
BT1, BT2: 3.7 V Lipo; BATTERY_18650-HOLDER
G back: LOGO
G front: LOGO
H4, H6: MountingHole_Pad; MountingHole_3.2mm_M3
J1: M5 2x15 pin; PinHeader_2x15_P2.54mm_Vertical
J2: Geiger IRover; PinHeader_1x03_P2.54mm_Vertical
J3: GPS; PinSocket_1x06_P2.54mm_Vertical
J4: Geiger Safepulse; PinHeader_1x03_P2.54mm_Vertical
J5: Extra support header; PinHeader_1x02_P2.54mm_Vertical
J6: Grove; PinSocket_1x04_P2.00mm_Horizontal
J7: QI GND out; PinHeader_1x01_P2.54mm_Vertical
J8: QI input GND; PinHeader_1x01_P2.54mm_Vertical
J9: QI battery out; PinHeader_1x01_P2.54mm_Vertical
J11: QI input +5V; PinHeader_1x01_P2.54mm_Vertical

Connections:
3.3V: J1.11, J2.1, J3.5, J4.3, J6.3
/BAT: BT1.1 (+), BT2.1 (+), J1.29, J9.1
/GIO2 on Core and GIO32 on Core-2: J1.20, J2.2, J4.2
/RX2: J1.15, J3.4
/SCL: J1.18, J3.6, J6.1
/SDA: J1.17, J3.1, J6.2
/TX2: J1.16, J3.3
GND: BT1.2 (-), BT2.2 (-), J1.2, J1.4, J1.6, J2.3, J3.2, J4.1, J6.4, J7.1, J8.1
